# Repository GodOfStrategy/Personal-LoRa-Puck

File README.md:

# Personal-LoRa-Module
A small compact module made to transmit and receive messages using sub gigahertzs frequencies of radio waves, for use in things such as automation, transmission, reception etc. I wanted to build this for a long time, because I want to implement noise pollution control using these modules, where one module will monitor honking >3 seconds and relay the information of the defaulter's vehicle to the receiver and fine the defaulter.

My LoRa module uses Sub GHz frequencies to tranceive radio waves. It uses the following components:
1. SX1262IMLTRT for transmission and reception.
2. RP2040 for Programing it for various applications.
3. 0900FM15D0039E as an RF filter.
4. AP2112K-3.3 as my LDO.
5. PE4259 as my RF switch.
6. Two quartz timer crystals (12 MHz and 32 MHz).
7. SMD Resistors.
8. SMD Capacitors.
9. SMD Inductors.
10. USB-C Receptacle.

Here is the Schematic:

Here is the PCB:

Here is the assembled PCB:

[Lora-BOM-2.csv](https://github.com/user-attachments/files/28879576/Lora-BOM-2.csv)
Please find the BOM and Firmware along with a 3D STEP file for my assembled PCB in my repo.

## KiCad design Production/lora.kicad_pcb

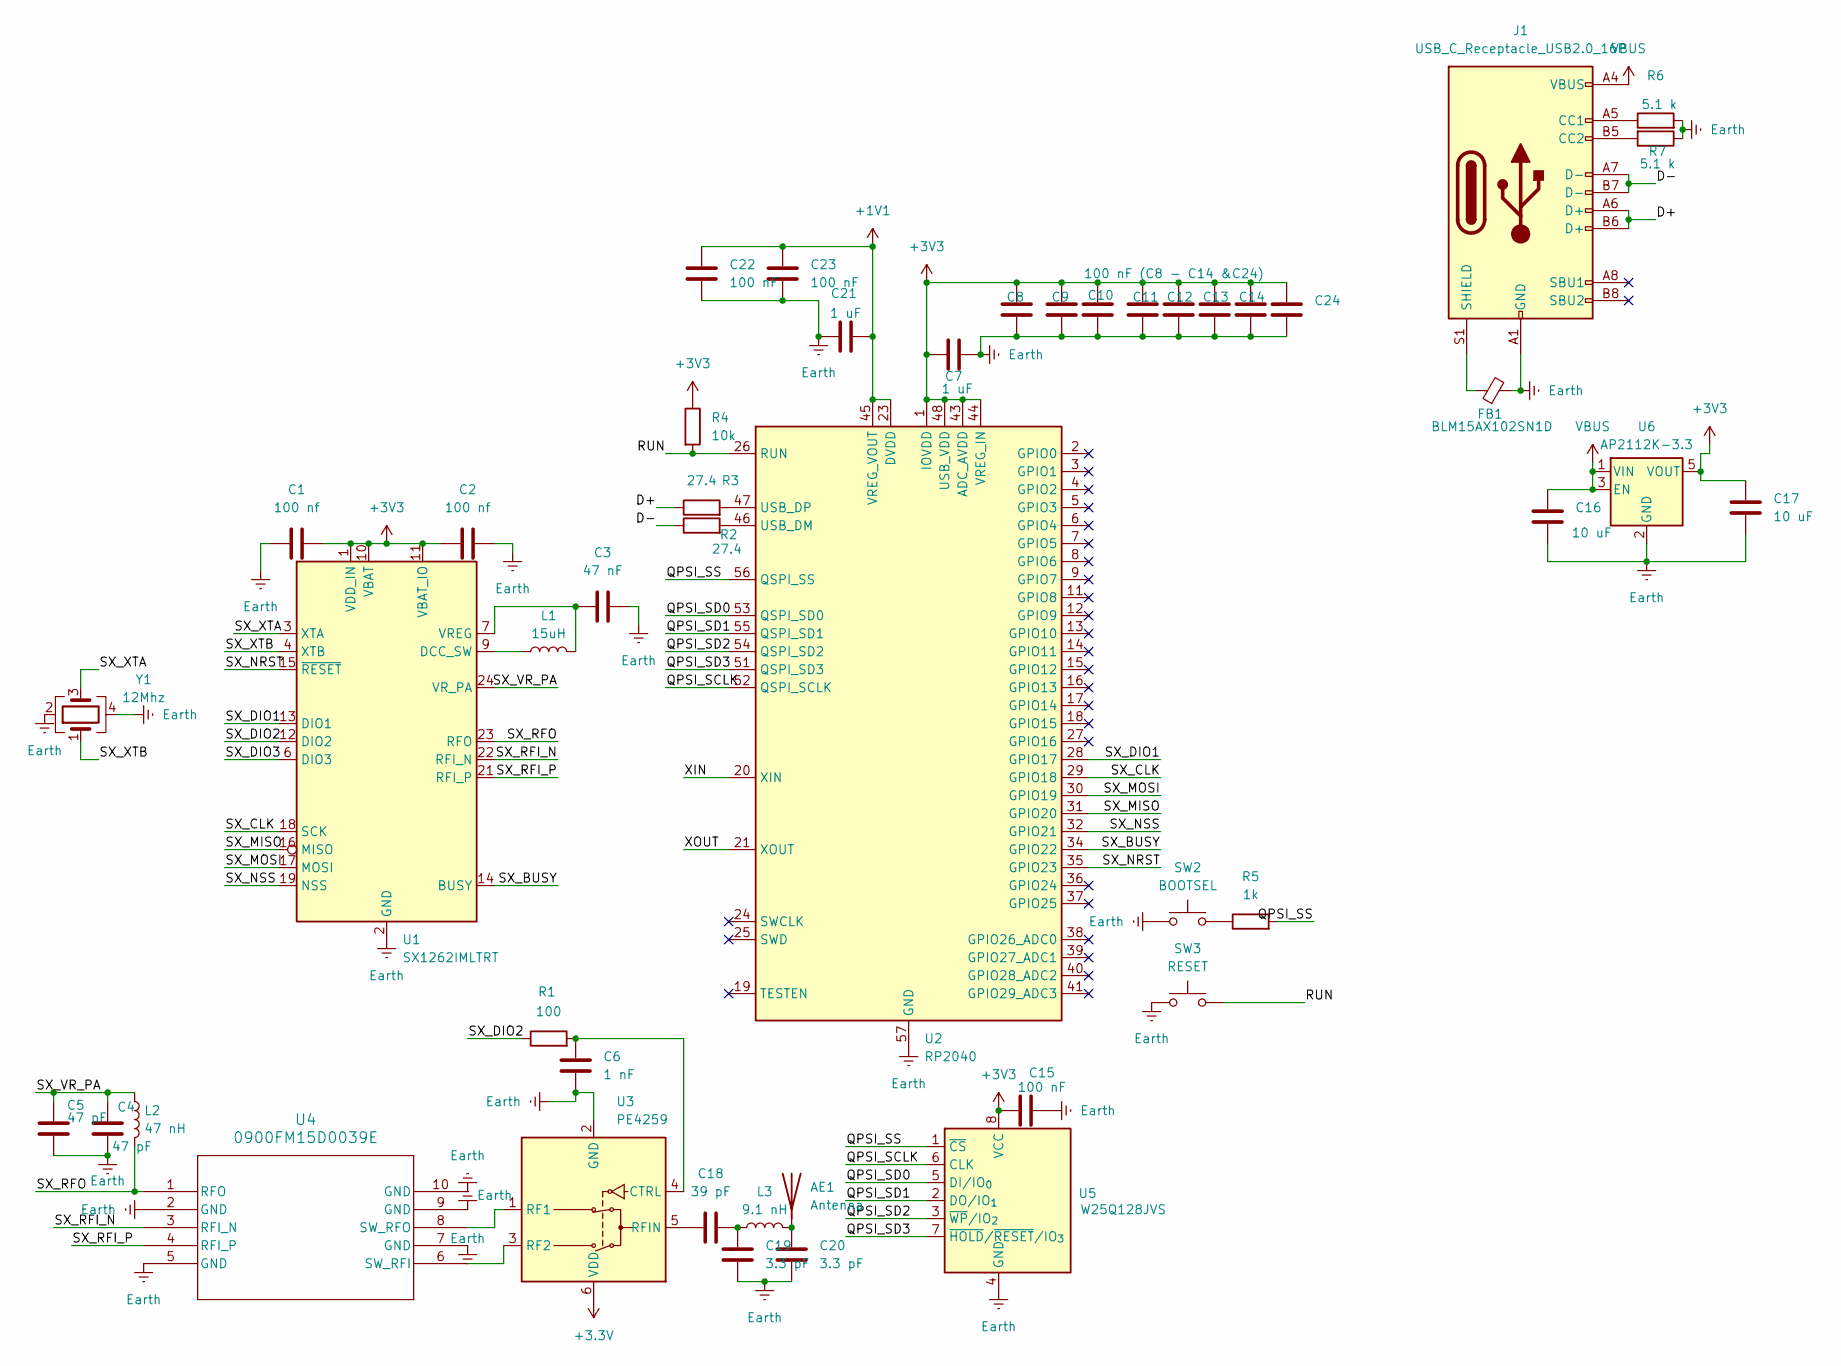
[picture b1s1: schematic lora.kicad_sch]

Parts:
AE1: Antenna; PinSocket_1x01_P2.54mm_Vertical
C1, C2: 100 nf; C_0402_1005Metric
C3: 47 nF; C_0402_1005Metric
C4, C5: 47 pF; C_0402_1005Metric
C6: 1 nF; C_0402_1005Metric
C7, C21: 1 uF; C_0402_1005Metric
C8, C9, C11, C12, C13, C14, C15, C22, C23: 100 nF; C_0402_1005Metric
C10: 100 nF (C8 - C14 &C24); C_0402_1005Metric
C16, C17: 10 uF; C_0402_1005Metric
C18: 39 pF; C_0402_1005Metric
C19, C20: 3.3 pF; C_0402_1005Metric
C24: 100nF; C_0402_1005Metric
FB1: BLM15AX102SN1D; L_0402_1005Metric
J1: USB_C_Receptacle_USB2.0_16P; USB_C_Receptacle_G-Switch_GT-USB-7010ASV
L1: 15uH; L_0201_0603Metric
L2: 47 nH; L_0402_1005Metric
L3: 9.1 nH; L_0402_1005Metric
R1: 100; R_0402_1005Metric
R2, R3: 27.4; R_0402_1005Metric
R4: 10k; R_0402_1005Metric
R5: 1k; R_0402_1005Metric
R6, R7: 5.1 k; R_0402_1005Metric
SW2: BOOTSEL; SW_SPST_PTS647_Sx70
SW3: RESET; SW_SPST_PTS647_Sx70
U1: SX1262IMLTRT; QFN-24-1EP_4x4mm_P0.5mm_EP2.6x2.6mm
U2: RP2040; QFN-56-1EP_7x7mm_P0.4mm_EP3.2x3.2mm
U3: PE4259; SOT-363_SC-70-6
U4: 0900FM15D0039E; Balun_Johanson_0900FM15K0039
U5: W25Q128JVS; SOIC-8_5.3x5.3mm_P1.27mm
U6: AP2112K-3.3; SOT-23-5
Y1: 12Mhz; Crystal_SMD_3225-4Pin_3.2x2.5mm

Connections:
+1V1: C21.2, C22.1, C23.1, U2.23 (DVDD), U2.45 (VREG_VOUT), U2.50 (DVDD)
+3.3V: U3.6 (VDD)
+3V3: C1.2, C2.1, C7.1, C8.1, C9.1, C10.1, C11.1, C12.1, C13.1, C14.1, C15.1, C17.1, C24.1, R4.1, U1.1 (VDD_IN), U1.10 (VBAT), U1.11 (VBAT_IO), U2.1 (IOVDD), U2.10 (IOVDD), U2.22 (IOVDD), U2.33 (IOVDD), U2.42 (IOVDD), U2.43 (ADC_AVDD), U2.44 (VREG_IN), U2.48 (USB_VDD), U2.49 (IOVDD), U5.8 (VCC), U6.5 (VOUT)
/D+: J1.A6 (D+), J1.B6 (D+), R3.1
/D-: J1.A7 (D-), J1.B7 (D-), R2.1
/QPSI_SCLK: U2.52 (QSPI_SCLK), U5.6 (CLK)
/QPSI_SD0: U2.53 (QSPI_SD0), U5.5 (DI/IO_{0})
/QPSI_SD1: U2.55 (QSPI_SD1), U5.2 (DO/IO_{1})
/QPSI_SD2: U2.54 (QSPI_SD2), U5.3 (~WP/IO_{2})
/QPSI_SD3: U2.51 (QSPI_SD3), U5.7 (~HOLD/~RESET/IO_{3})
/QPSI_SS: R5.2, U2.56 (QSPI_SS), U5.1 (~CS)
/RUN: R4.2, SW3.2, U2.26 (RUN)
/SX_BUSY: U1.14 (BUSY), U2.34 (GPIO22)
/SX_CLK: U1.18 (SCK), U2.29 (GPIO18)
/SX_DIO1: U1.13 (DIO1), U2.28 (GPIO17)
/SX_DIO2: R1.1, U1.12 (DIO2)
/SX_DIO3: U1.6 (DIO3)
/SX_MISO: U1.16 (MISO), U2.31 (GPIO20)
/SX_MOSI: U1.17 (MOSI), U2.30 (GPIO19)
/SX_NRST: U1.15 (~RESET), U2.35 (GPIO23)
/SX_NSS: U1.19 (NSS), U2.32 (GPIO21)
/SX_RFI_N: U1.22 (RFI_N), U4.3 (RFI_N)
/SX_RFI_P: U1.21 (RFI_P), U4.4 (RFI_P)
/SX_RFO: L2.2, U1.23 (RFO), U4.1 (RFO)
/SX_VR_PA: C4.1, C5.1, L2.1, U1.24 (VR_PA)
/SX_XTA: U1.3 (XTA), Y1.3
/SX_XTB: U1.4 (XTB), Y1.1
/XIN: U2.20 (XIN)
/XOUT: U2.21 (XOUT)
Earth: C1.1, C2.2, C3.2, C4.2, C5.2, C6.2, C7.2, C8.2, C9.2, C10.2, C11.2, C12.2, C13.2, C14.2, C15.2, C16.1, C17.2, C19.2, C20.2, C21.1, C22.2, C23.2, C24.2, FB1.2, J1.A1 (GND), J1.A12 (GND), J1.B1 (GND), J1.B12 (GND), R6.2, R7.1, SW2.1, SW3.1, U1.2 (GND), U1.5 (GND), U1.8 (GND), U1.20 (GND), U1.25 (GND), U2.57 (GND), U3.2 (GND), U4.2 (GND), U4.5 (GND), U4.7 (GND), U4.9 (GND), U4.10 (GND), U5.4 (GND), U6.2 (GND), Y1.2, Y1.4
unnamed: AE1.1 (A), C20.1, L3.2
unnamed: C18.2, C19.1, L3.1
unnamed: J1.A5 (CC1), R6.1
unnamed: J1.B5 (CC2), R7.2
unnamed: FB1.1, J1.S1 (SHIELD)
unnamed: R5.1, SW2.2
unnamed: L1.1, U1.9 (DCC_SW)
unnamed: C3.1, L1.2, U1.7 (VREG)
unnamed: R2.2, U2.46 (USB_DM)
unnamed: R3.2, U2.47 (USB_DP)
unnamed: C6.1, R1.2, U3.4 (CTRL)
unnamed: U3.1 (RF1), U4.8 (SW_RFO)
unnamed: U3.3 (RF2), U4.6 (SW_RFI)
unnamed: C18.1, U3.5 (RFIN)
VBUS: C16.2, J1.A4 (VBUS), J1.A9 (VBUS), J1.B4 (VBUS), J1.B9 (VBUS), U6.1 (VIN), U6.3 (EN)

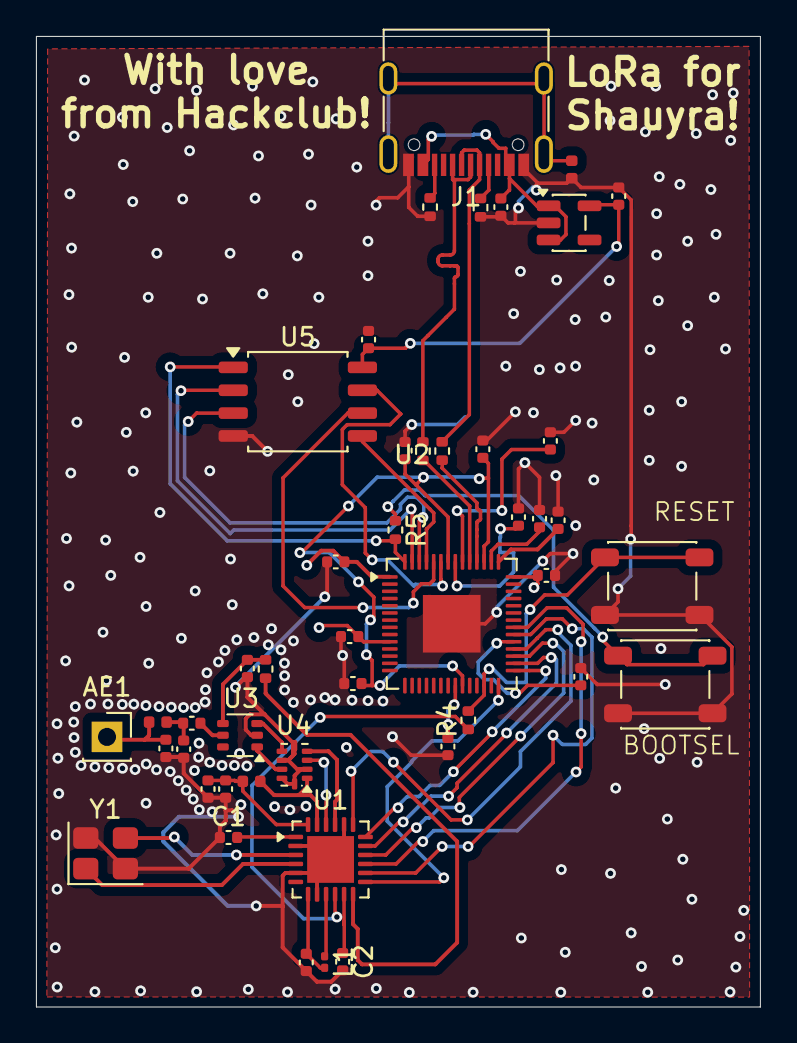
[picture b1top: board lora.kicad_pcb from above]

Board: 4 copper layers, 40.2 x 53.9 mm, 46 parts (0 on the bottom side), 41 nets.

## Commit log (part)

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2026-02-12 Create a
2026-02-12 Create Directions to installing your own Firmware
2026-03-31 Update BOM reference in README
